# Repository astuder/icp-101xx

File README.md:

# ICP-101xx Library and Breakout Board

The TDK InvenSense ICP-101xx is a family of very low power, very high accuracy barometric pressure sensors. These sensors can measure pressure difference of as little as +/- 1 Pascal, which is equivalent to altitude differences of 8.5cm.

Documentation by TDK InvenSense:
* Product pages and datasheets: [TDK InvenSense](https://invensense.tdk.com/smartpressure/)
* Application Note: [Differential Pressure Sensing for Drones](https://www.invensense.com/download-pdf/an-000119-differential-pressure-sensing-using-icm-20789-for-altitude-hold-in-drones/)

Besides the [library for Arduino](#arduino-library), this repository also includes basic libraries compatible with the STM32 HAL [here](./extras/stm32-hal) and Mbed OS [here](./extras/mbed), and KiCad projects for [three breakout boards](#breakout-boards).

## Arduino Library

The Arduino library ICP101xx provides a simple API to read temperature and pressure. The library was developed and tested with the ICP-10100 and ICP-10125 but should also work with other sensors of the family.

The library includes 3 examples that demonstrate its use.

### The ICP101xx Object

Use the `ICP101xx` object to create an instance of the sensor. For example, by declaring a global variable:

```
ICP101xx mysensor;
```

### begin()

To initialize the sensor, use the `begin` method.

```
mysensor.begin();
```

By default, the sensor will use the Arduino `Wire` object for I2C. If you want to use the sensor on a different I2C port, pass a pointer to the `Wire` object the library should use. For example:

```
mysensor.begin(&Wire1);
```

The `begin` method connects to the sensor and reads the calibration data. It will return `false`, if the sensor does not respond. This can be used for error handling.

```
if (!mysensor.begin()) {
	// sensor did not respond, do error handling here
}
```

### isConnected()

This method is used to check whether the sensor is responding. This method returns `true` if the sensor can be reached.

```
if (mysensor.isConnected()) {
	// do some measurements
} else {
	// report an error
}
```

`isConnected` will return false in the following situations:

- No response from the sensor. Check your connections and pull-up resistors.
- Sensor responds with an unknown or unsupported device ID.

### measure()

The method `measure` performs a measurement and doesn't return control until the measurement is completed.

The time to complete a measurement depends on the selected sensor mode that can be passed as an optional parameter. The options are:

|Mode|Duration|Noise|[Sensor Mode](http://www.invensense.com/wp-content/uploads/2019/02/DS-000186-ICP-101xx-v1.1.pdf#%5B%7B%22num%22%3A12%2C%22gen%22%3A0%7D%2C%7B%22name%22%3A%22XYZ%22%7D%2C34%2C530%2C0%5D)|Notes|
|--|--|--|--|--|
|FAST|3 ms|±3.2 Pa|Low Power (LP)| |
|NORMAL|7 ms|±1.6 Pa|Normal (N)|default|
|ACCURATE|24 ms|±0.8 Pa|Low Noise (LN)| |
|VERY_ACCURATE|95 ms|±0.4 Pa|Ultra Low Noise (ULN)| |

```
mysensor.measure(mysensor.VERY_ACCURATE);	// high accuracy measurement
// process data
```

If mode is not specified, NORMAL will be used.

```
mysensor.measure();	  // normal measurement
// process data
```

### measureStart(), dataReady()

Sometimes you may not want to wait idly until a measurement is complete but do something useful while the sensor is busy. Especially when using the VERY_ACCURATE mode, which takes almost 100ms to complete.

`measureStart` initiates a new measurement and immediately returns control to the calling program. Like the method `measure`, an optional parameter can be used to specify the accuracy. You can then use `dataReady` to check whether the sensor completed its task.

```
mysensor.measureStart(mysensor.VERY_ACCURATE);
while (!mysensor.dataReady()) {
	// do some other useful stuff
}
// the sensor is done, process the data
```

### getPressurePa()

When measurement is complete, the result is stored in the sensor object and can be read with the `getPressurePa` method.

`getPressurePa` returns the pressure in Pascal (Pa) as a `float`.

```
mysensor.measure();
Serial.print("Pressure is ");
Serial.print(mysensor.getPressurePa());
Serial.println(" Pa");
```

Pascal is mostly of interest to measure tiny pressure differences. For absolute pressure, you may want to apply some simple math.

|Target unit|Formula|
|--|--|
|hPa|Pa / 100|
|mbar|Pa / 100|
|mmHg|Pa / 133.322365|
|inHg|Pa / 3386.389|
|atm|Pa / 101325|

### getTemperatureC(), getTemperatureF()

The ICP-101xx also includes a very precise temperature sensor with an absolute accuracy of ±0.4 Celsius. The temperature is sampled together with the pressure during each measurement cycle. Use `getTemperatureC` or `getTemperatureF` to get the temperature as `float` in Celsius or Fahrenheit respectively.

```
mysensor.measure();
Serial.print("The current temperature is ");
Serial.print(mysensor.getTemperatureF());
Serial.println(" Fahrenheit");
```

## Breakout Boards

This repository includes the design files for three breakout boards in the folder [extras/KiCad](./extras/KiCad). These breakout boards were designed with Kicad 5.x. 

The ICP-101xx is a 1.8V part, but the boards include a voltage regulator and I2C level-shifter. This allows to interface the sensor to 2.8V, 3.3V or 5V logic.

Soldering the sensor requires a solder paste stencil and reflow oven or hotplate, though experienced tinkerers may manage to assemble it only using a hot air station.

Contact me if you are interested in buying populated and tested breakout boards, I may have a few at hand. There's also an inexpensive breakout board by [Mikroe](https://www.mikroe.com/altitude-3-click) (search `MIKROE-3328` on Digi-Key, Mouser and other distributors), which should work with this library.

### ICP-10100 Breakout

The sensor can be separated from the rest of the breakout board, for example to put into confined and/or exposed spaces.

You can order the PCB on [OSH Park](https://oshpark.com/shared_projects/2vvKCdQE)

### ICP-10100 Probe

A probe style breakout board, ideal to shove the sensor into narrow places.

This design works best with very thin or flexible PCB material.

You can order the PCB on [OSH Park](https://oshpark.com/shared_projects/IjXrtBOE)

### ICP-10125 Breakout

A breakout board for the new [ICP-10125](https://invensense.tdk.com/products/1-axis/icp-10125/) pressure sensor.

This part is larger than the ICP-10100 and may be easier to assemble, though the pads are still under the component.

You can order the PCB on [OSH Park](https://oshpark.com/shared_projects/CTwkdHlc)

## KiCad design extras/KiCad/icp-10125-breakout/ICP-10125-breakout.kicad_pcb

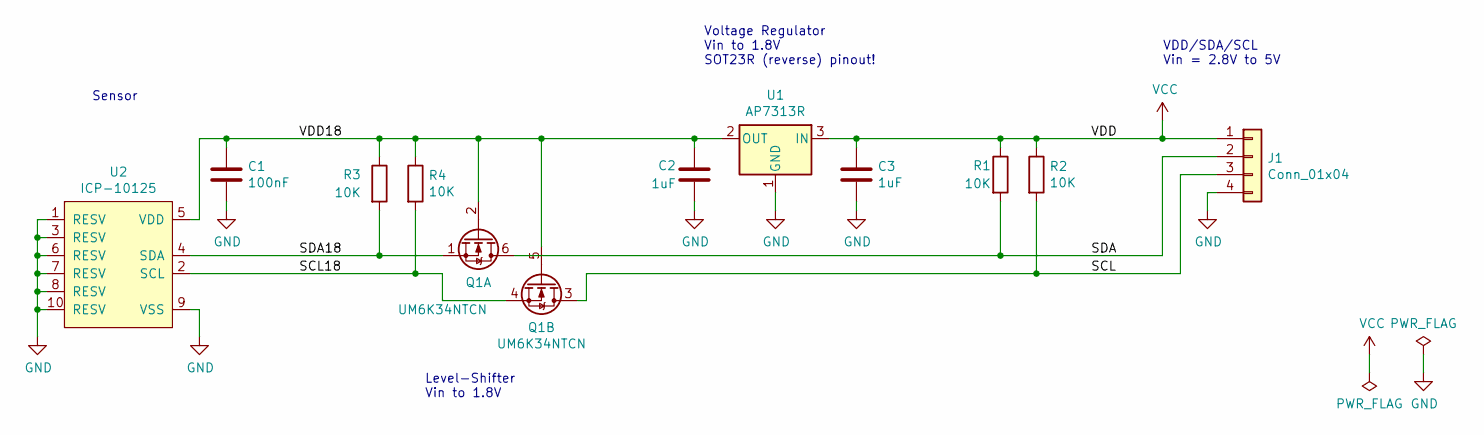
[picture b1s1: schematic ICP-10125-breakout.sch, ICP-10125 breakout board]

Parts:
C1: 100nF; C_0603_1608Metric
C2, C3: 1uF; C_0603_1608Metric
J1: Conn_01x04; PinHeader_1x04_P2.54mm_Vertical
Q1: UM6K34NTCN; SOT-363_SC-70-6; Mpn UM6K34NTCN
R1, R2, R3, R4: 10K; R_0603_1608Metric
U1: AP7313R; SOT-23; Mpn AP7313-18SRG-7
U2: ICP-10125; Mpn ICP-10125

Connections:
/SCL: J1.3, Q1.3 (D), R2.2
/SCL18: Q1.4 (S), R4.2, U2.2 (SCL)
/SDA: J1.2, Q1.6 (D), R1.2
/SDA18: Q1.1 (S), R3.2, U2.4 (SDA)
/VDD18: C1.1, C2.1, Q1.2 (G), Q1.5 (G), R3.1, R4.1, U1.2 (OUT), U2.5 (VDD)
GND: C1.2, C2.2, C3.2, J1.4, U1.1 (GND), U2.1 (RESV), U2.3 (RESV), U2.6 (RESV), U2.7 (RESV), U2.8 (RESV), U2.9 (VSS), U2.10 (RESV)
VCC: C3.1, J1.1, R1.1, R2.1, U1.3 (IN)

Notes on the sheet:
Voltage Regulator Vin to 1.8V SOT23R (reverse) pinout!
Level-Shifter Vin to 1.8V
Sensor
VDD/SDA/SCL Vin = 2.8V to 5V

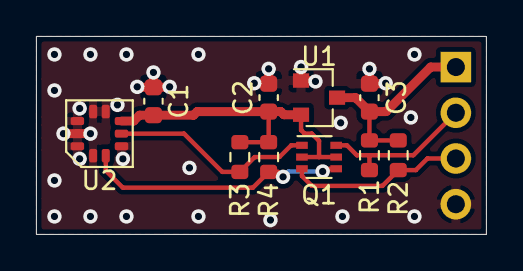
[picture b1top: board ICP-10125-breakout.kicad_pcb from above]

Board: 2 copper layers, 25.0 x 11.0 mm, 11 parts (1 on the bottom side), 7 nets.

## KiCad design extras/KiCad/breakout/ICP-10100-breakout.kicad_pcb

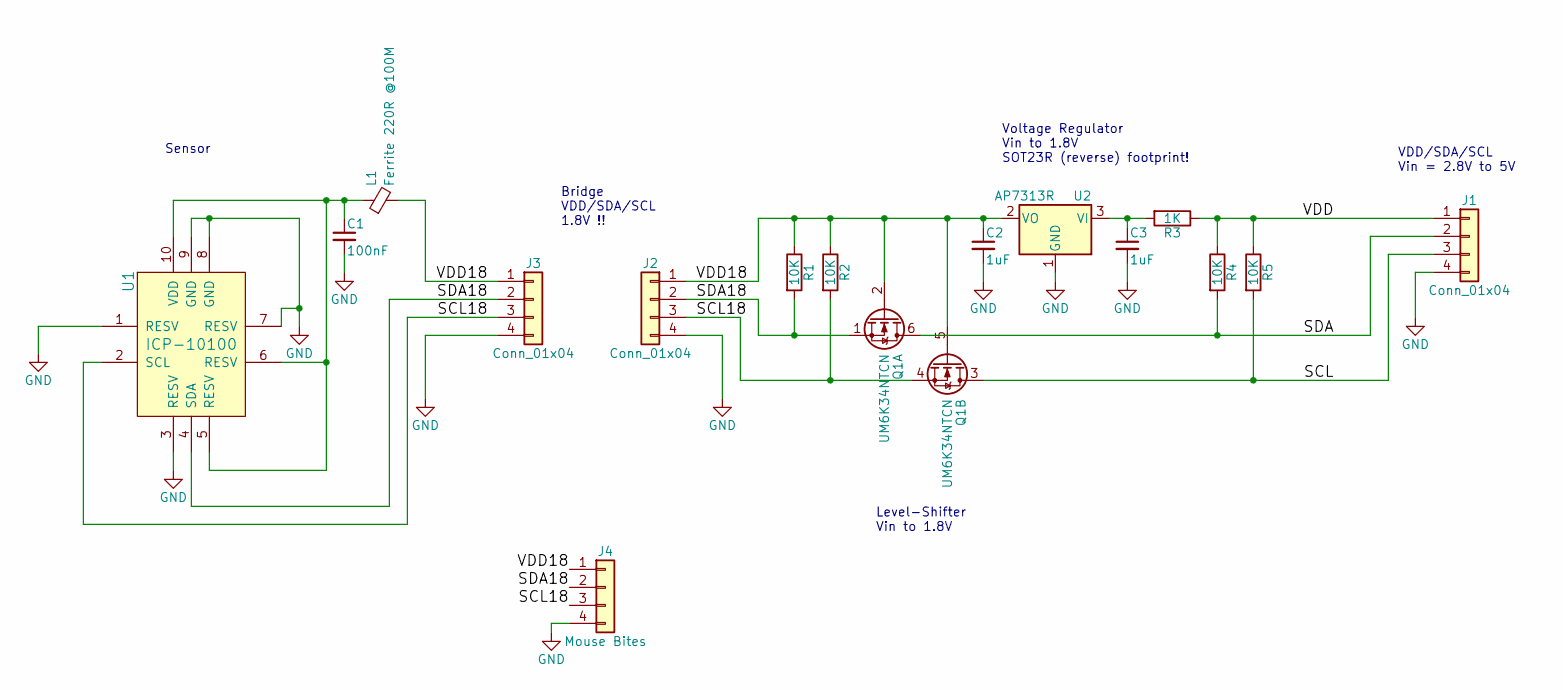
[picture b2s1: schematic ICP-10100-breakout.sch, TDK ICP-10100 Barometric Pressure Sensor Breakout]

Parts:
C1: 100nF; C_0603_1608Metric
C2, C3: 1uF; C_0603_1608Metric
J1, J2, J3: Conn_01x04; PinHeader_1x04_P2.54mm_Vertical
J4: Mouse Bites; Bites
L1: Ferrite 220R @100M; C_0603_1608Metric; Mpn BLM18PG221SN1D
Q1: UM6K34NTCN; SOT-363_SC-70-6; Mpn UM6K34NTCN
R1, R2, R4, R5: 10K; R_0603_1608Metric
R3: 1K; R_0603_1608Metric
U1: ICP-10100; Mpn ICP-10100
U2: AP7313R; SOT-223-3_TabPin2; Mpn AP7313-18SRG-7

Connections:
/SCL: J1.3, Q1.3 (D), R5.2
/SCL18: J2.3, J3.3, J4.3, Q1.4 (S), R2.2, U1.2 (SCL)
/SDA: J1.2, Q1.6 (D), R4.2
/SDA18: J2.2, J3.2, J4.2, Q1.1 (S), R1.2, U1.4 (SDA)
/VDD: J1.1, R3.1, R4.1, R5.1
/VDD18: C2.1, J2.1, J3.1, J4.1, L1.2, Q1.2 (G), Q1.5 (G), R1.1, R2.1, U2.2 (VO)
GND: C1.2, C2.2, C3.2, J1.4, J2.4, J3.4, J4.4, U1.1 (RESV), U1.3 (RESV), U1.7 (RESV), U1.8 (GND), U1.9 (GND), U2.1 (GND)
unnamed: C1.1, L1.1, U1.5 (RESV), U1.6 (RESV), U1.10 (VDD)
unnamed: C3.1, R3.2, U2.3 (VI)

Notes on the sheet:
VDD/SDA/SCL Vin = 2.8V to 5V
Bridge VDD/SDA/SCL 1.8V !!
Voltage Regulator Vin to 1.8V SOT23R (reverse) footprint!
Level-Shifter Vin to 1.8V
Sensor

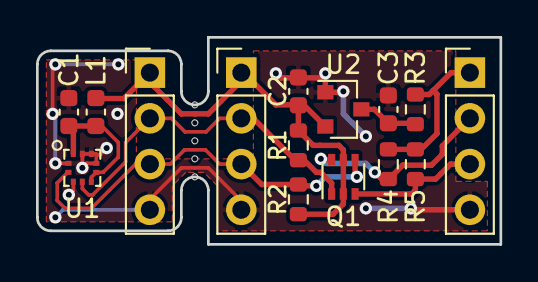
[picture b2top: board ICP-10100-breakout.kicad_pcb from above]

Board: 2 copper layers, 25.8 x 11.5 mm, 16 parts (0 on the bottom side), 9 nets.

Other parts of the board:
BITE: Bites2

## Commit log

2018-03-13 Arduino library for ICP-101xx
2018-03-13 Example data plot
2018-03-15 documented library
2018-03-15 fix table, add readTemperatureF
2018-03-15 typos
2018-03-16 add missing includes
2018-03-18 remove unused variable
2018-05-23 add hardware files
2018-06-13 Use correct separator in keywords.txt
    The Arduino IDE currently requires the use of a single true tab separator between the name and identifier. Without this tab the keyword is not highlighted.
    Reference:
    https://github.com/arduino/Arduino/wiki/Arduino-IDE-1.5:-Library-specification#keywords
2018-06-18 Move library to root of repository
    A popular library installation technique is to download the library via GitHub's Clone or download > Download ZIP and then use the Arduino IDE's Sketch > Include Library > Add .ZIP Library on the dow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
    Specified folder/zip file does not contain a valid library
    This move is also required if you wanted to add your library to the Arduino Library Manager index, which provides an even easier installation option.
2018-06-28 fixed issue #3
2018-07-07 fix pressure calculation for AVR Arduinos issue #4
2018-07-08 added Arduino library descriptor
2018-07-14 Fixed documentation
2019-02-21 Fixed links to product page and datasheet
2019-02-21 Clarified measurement modes
2019-12-18 update getPressure example
2020-12-02 add library compatible with STM32 HAL to extras
2020-12-02 fixed title for STM32 library
2021-02-05 copy of stm32 hal
2021-02-05 adaptations for mbedOS
2021-02-05 Update title
2021-02-05 Add link to Mbed library
2021-03-10 reorganized and updated CAD files, added flex probe
2021-03-10 minor edits
2021-05-23 add note about reversed footprint of LDO
2021-05-23 updated PDFs of schematic
2021-08-18 tested with ICP-10125
2021-08-19 add part number for L1, clean-up metadata
2021-08-19 add ICP-10125 breakout board
